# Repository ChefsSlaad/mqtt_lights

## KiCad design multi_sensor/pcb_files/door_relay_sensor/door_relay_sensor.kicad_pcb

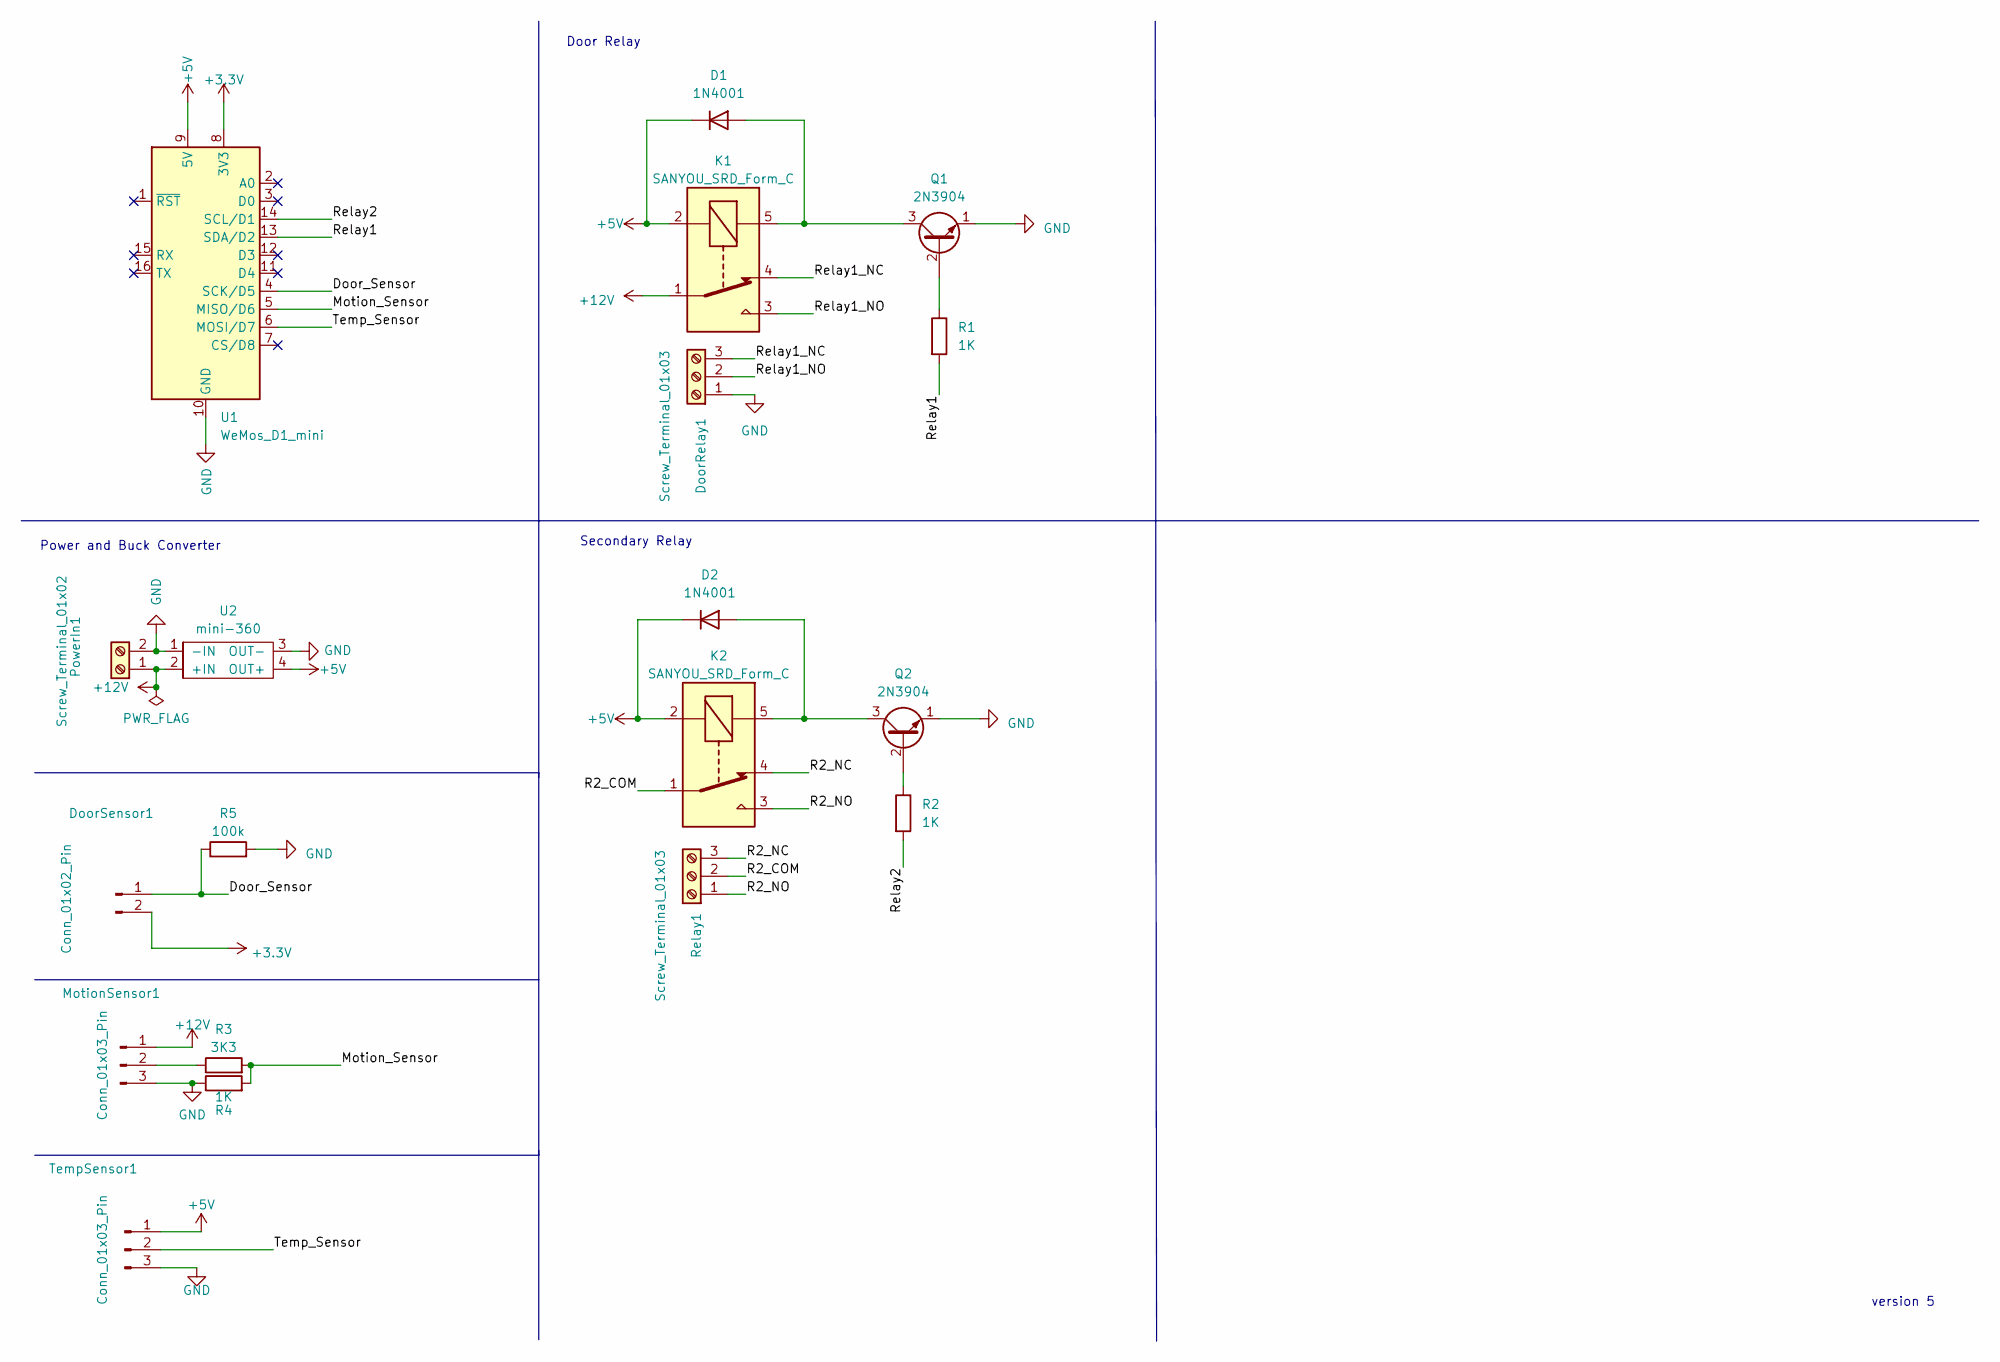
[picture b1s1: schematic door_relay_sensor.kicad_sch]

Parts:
D1, D2: 1N4001; D_DO-41_SOD81_P7.62mm_Horizontal
DoorRelay1: Screw_Terminal_01x03; TerminalBlock_bornier-3_P5.08mm
DoorSensor1: Conn_01x02_Pin; JST_EH_B2B-EH-A_1x02_P2.50mm_Vertical
K1, K2: SANYOU_SRD_Form_C; Relay_SPDT_SANYOU_SRD_Series_Form_C
MotionSensor1: Conn_01x03_Pin; JST_EH_B3B-EH-A_1x03_P2.50mm_Vertical
PowerIn1: Screw_Terminal_01x02; TerminalBlock_bornier-2_P5.08mm
Q1, Q2: 2N3904; TO-92_Wide
R1, R2, R4: 1K; R_Axial_DIN0207_L6.3mm_D2.5mm_P7.62mm_Horizontal
R3: 3K3; R_Axial_DIN0207_L6.3mm_D2.5mm_P7.62mm_Horizontal
R5: 100k; R_Axial_DIN0207_L6.3mm_D2.5mm_P7.62mm_Horizontal
Relay1: Screw_Terminal_01x03; TerminalBlock_bornier-3_P5.08mm
TempSensor1: Conn_01x03_Pin; JST_EH_B3B-EH-A_1x03_P2.50mm_Vertical
U1: WeMos_D1_mini; WEMOS_D1_mini_light
U2: mini-360; buck_converter 16.8x22,14

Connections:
+3.3V: DoorSensor1.2, U1.8 (3V3)
+5V: D1.1 (K), D2.1 (K), K1.2, K2.2, TempSensor1.1, U1.9 (5V), U2.4 (OUT+)
+12V: K1.1, MotionSensor1.1, PowerIn1.1, U2.2 (+IN)
/Door_Sensor: DoorSensor1.1, R5.1, U1.4 (SCK/D5)
/Motion_Sensor: R3.2, R4.2, U1.5 (MISO/D6)
/R2_COM: K2.1, Relay1.2
/R2_NC: K2.4, Relay1.3
/R2_NO: K2.3, Relay1.1
/Relay1: R1.2, U1.13 (SDA/D2)
/Relay1_NC: DoorRelay1.3, K1.4
/Relay1_NO: DoorRelay1.2, K1.3
/Relay2: R2.2, U1.14 (SCL/D1)
/Temp_Sensor: TempSensor1.2, U1.6 (MOSI/D7)
GND: DoorRelay1.1, MotionSensor1.3, PowerIn1.2, Q1.1 (E), Q2.1 (E), R4.1, R5.2, TempSensor1.3, U1.10 (GND), U2.1 (-IN), U2.3 (OUT-)
unnamed: D1.2 (A), K1.5, Q1.3 (C)
unnamed: D2.2 (A), K2.5, Q2.3 (C)
unnamed: MotionSensor1.2, R3.1
unnamed: Q1.2 (B), R1.1
unnamed: Q2.2 (B), R2.1

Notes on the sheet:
Power and Buck Converter
Secondary Relay
version 5
Door Relay

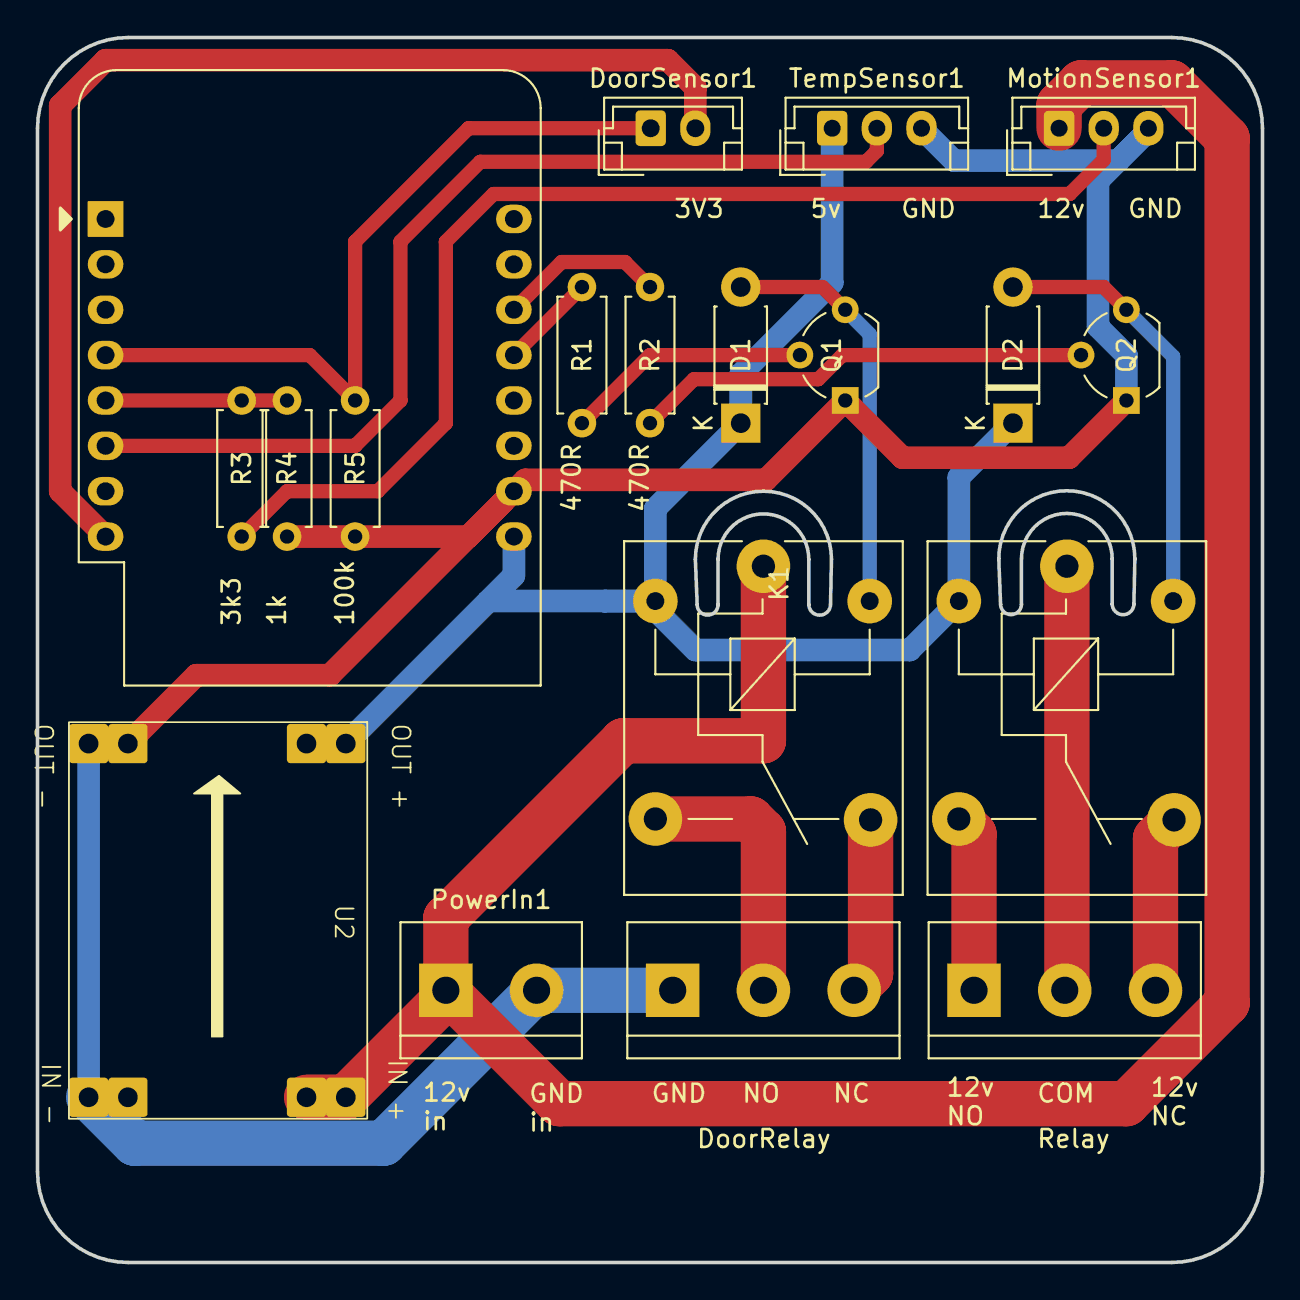
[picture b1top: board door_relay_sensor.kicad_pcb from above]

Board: 2 copper layers, 68.6 x 68.6 mm, 19 parts (0 on the bottom side), 19 nets.

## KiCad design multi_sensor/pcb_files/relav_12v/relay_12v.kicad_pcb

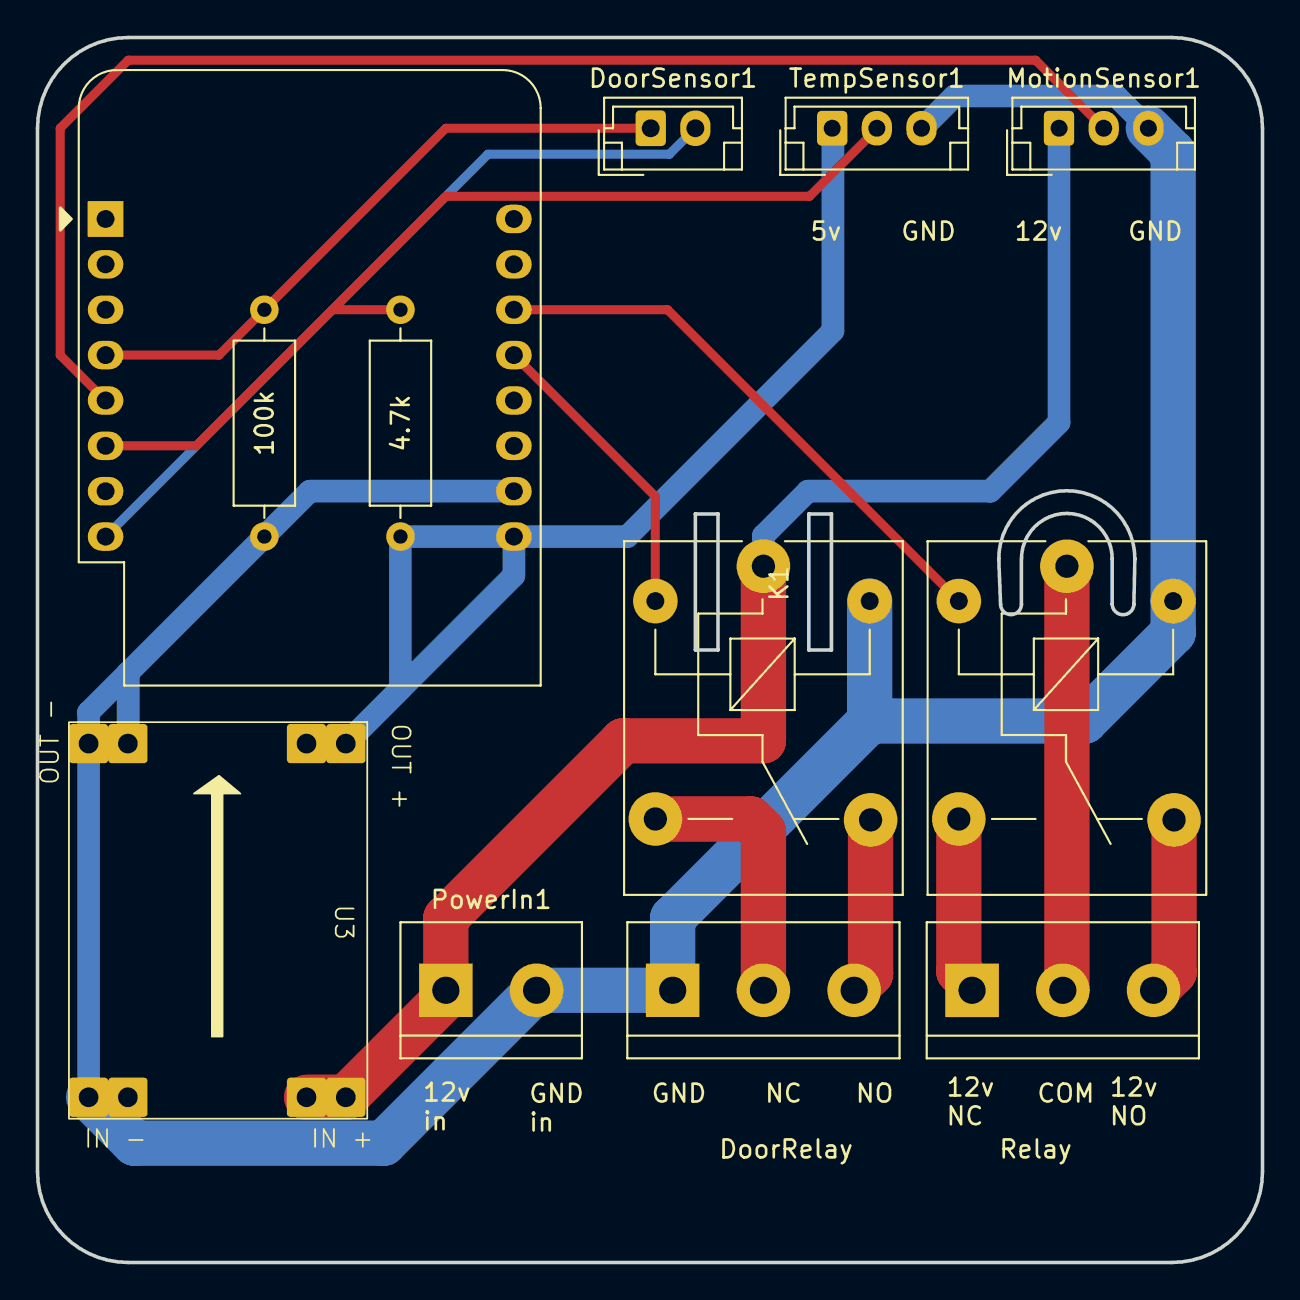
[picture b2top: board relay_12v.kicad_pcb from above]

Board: 2 copper layers, 68.6 x 68.6 mm, 12 parts (0 on the bottom side), 14 nets.

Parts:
DoorRelay: Screw_Terminal_01x03; TerminalBlock_bornier-3_P5.08mm
DoorSensor1: Conn_01x02_Pin; JST_EH_B2B-EH-A_1x02_P2.50mm_Vertical
K1, K2: SANYOU_SRD_Form_C; Relay_SPDT_SANYOU_SRD_Series_Form_C
MotionSensor1: Conn_01x03_Pin; JST_EH_B3B-EH-A_1x03_P2.50mm_Vertical
PowerIn1: Screw_Terminal_01x02; TerminalBlock_bornier-2_P5.08mm
R1: 100k; R_Axial_DIN0309_L9.0mm_D3.2mm_P12.70mm_Horizontal
R2: 4.7k; R_Axial_DIN0309_L9.0mm_D3.2mm_P12.70mm_Horizontal
Relay: Screw_Terminal_01x03; TerminalBlock_bornier-3_P5.08mm
TempSensor1: Conn_01x03_Pin; JST_EH_B3B-EH-A_1x03_P2.50mm_Vertical
U1: WeMos_D1_mini; WEMOS_D1_mini_light
U3: mini-360; buck_converter 16.8x22,14

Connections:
+3.3V: DoorSensor1.2, U1.8 (3V3)
+5V: R2.1, TempSensor1.1, U1.9 (5V), U3.4 (OUT+)
+12V: K1.1, MotionSensor1.1, PowerIn1.1, U3.2 (+IN)
/Door_Sensor: DoorSensor1.1, R1.1, U1.4 (SCK/D5)
/Motion_Sensor: MotionSensor1.2, U1.5 (MISO/D6)
/R2_COM: K2.1, Relay.2
/R2_NC: K2.4, Relay.3
/R2_NO: K2.3, Relay.1
/Relay1: K1.2, U1.13 (SDA/D2)
/Relay1_NC: DoorRelay.3, K1.4
/Relay1_NO: DoorRelay.2, K1.3
/Relay2: K2.2, U1.14 (SCL/D1)
/Temp_Sensor: R2.2, TempSensor1.2, U1.6 (MOSI/D7)
GND: DoorRelay.1, K1.5, K2.5, MotionSensor1.3, PowerIn1.2, R1.2, TempSensor1.3, U1.10 (GND), U3.1 (-IN), U3.3 (OUT-)

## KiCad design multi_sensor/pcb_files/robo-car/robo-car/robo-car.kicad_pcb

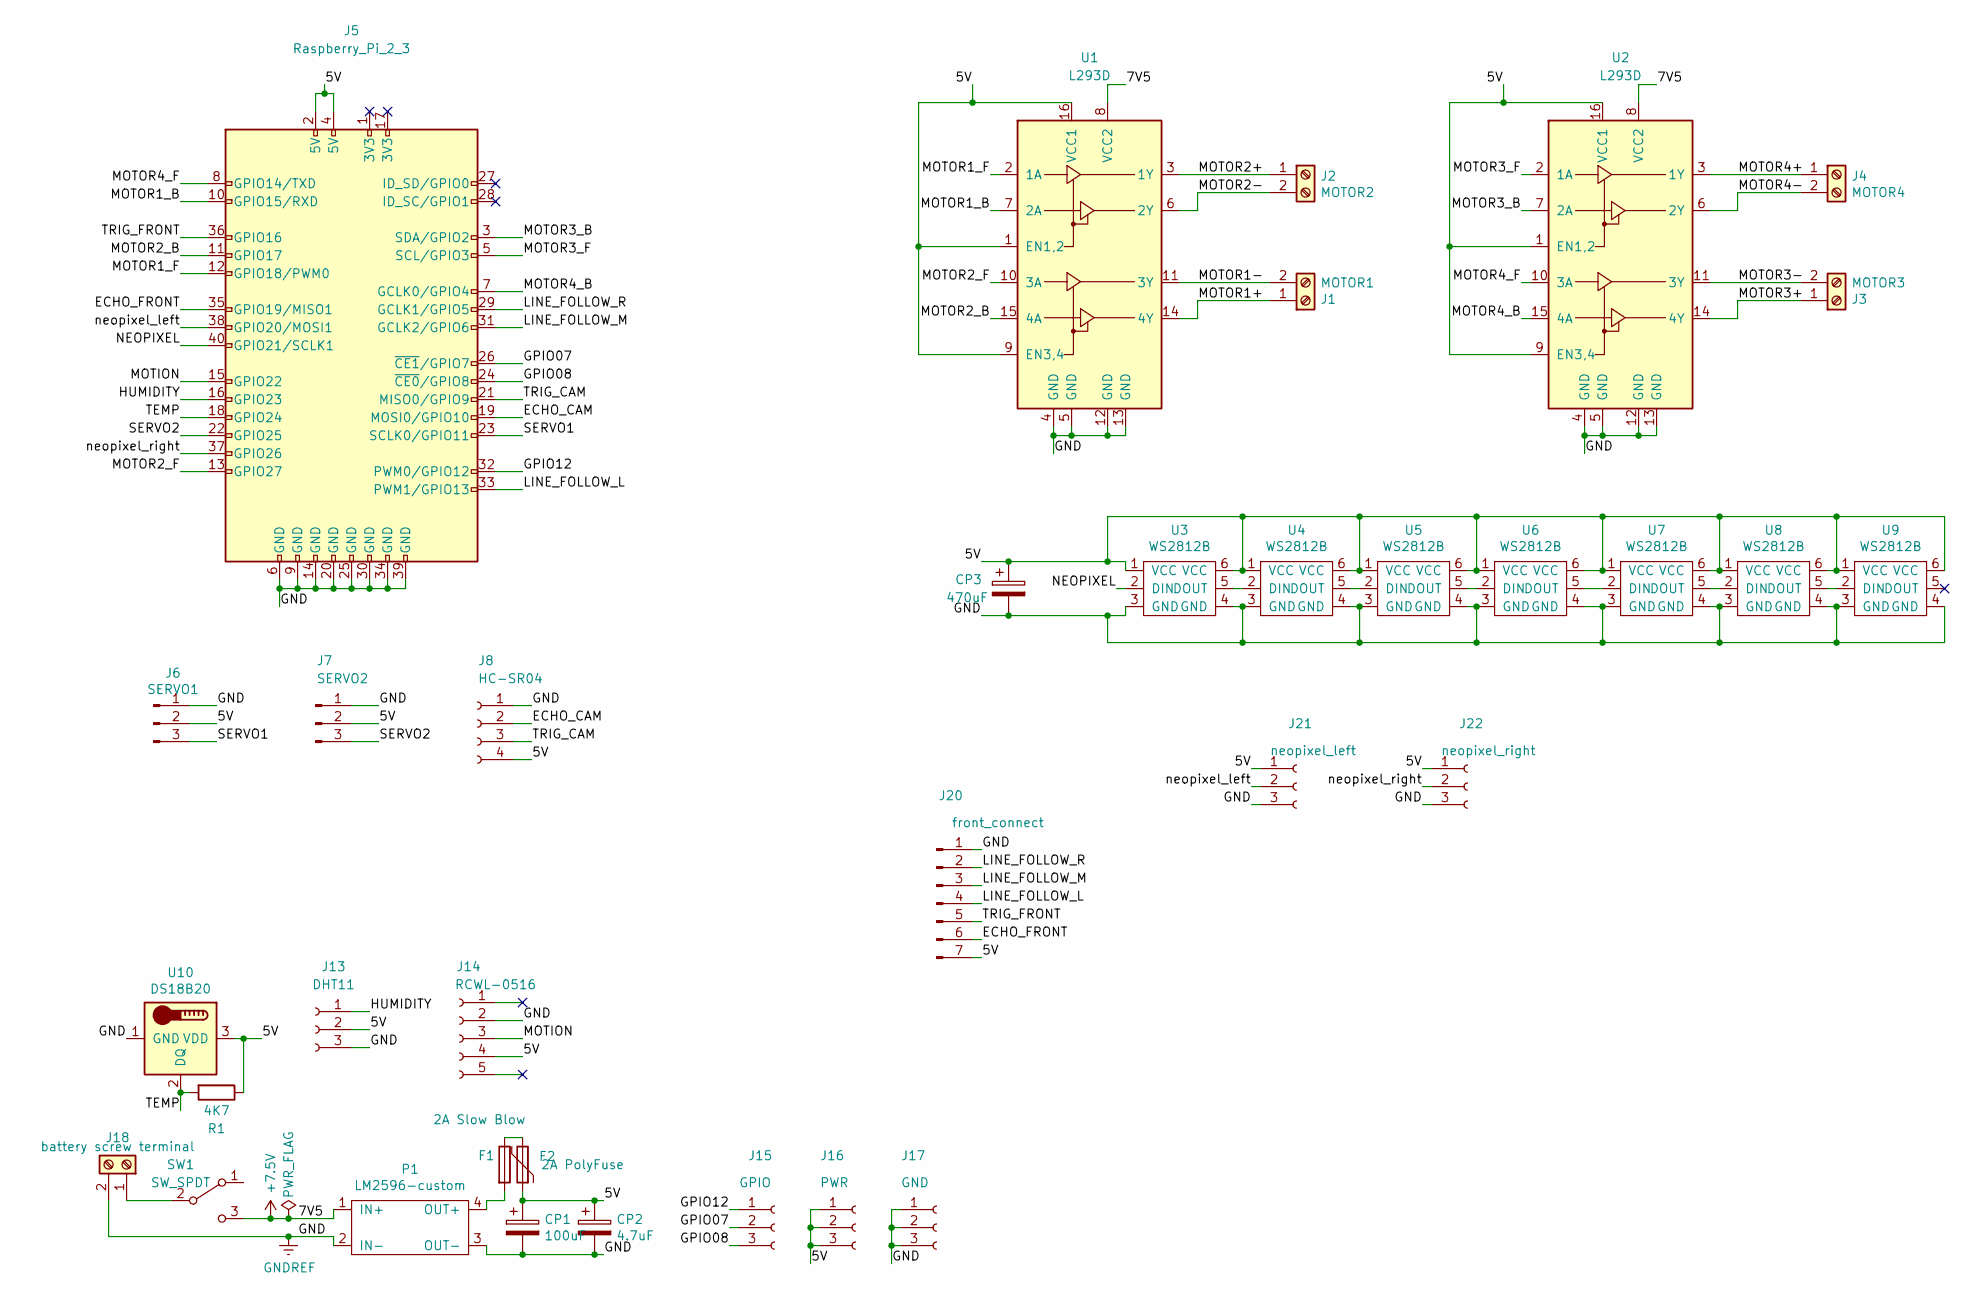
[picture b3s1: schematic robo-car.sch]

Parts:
CP1: 100uF; CP_Radial_D5.0mm_P2.50mm
CP2: 4.7uF; CP_Radial_D4.0mm_P2.00mm
CP3: 470uF; CP_Radial_D6.3mm_P2.50mm
F1: 2A Slow Blow; slow_blow_polyfuse
F2: 2A PolyFuse; restoring polyfuse
J1: MOTOR1; TerminalBlock_Altech_AK300-2_P5.00mm
J2: MOTOR2; TerminalBlock_Altech_AK300-2_P5.00mm
J3: MOTOR3; TerminalBlock_Altech_AK300-2_P5.00mm
J4: MOTOR4; TerminalBlock_Altech_AK300-2_P5.00mm
J5: Raspberry_Pi_2_3; PinSocket_2x20_P2.54mm_Vertical
J6: SERVO1; PinHeader_1x03_P2.54mm_Vertical
J7: SERVO2; PinHeader_1x03_P2.54mm_Vertical
J8: HC-SR04; PinSocket_1x04_P2.54mm_Vertical
J13: DHT11; PinSocket_1x03_P2.54mm_Vertical
J14: RCWL-0516; PinHeader_1x05_P2.54mm_Vertical
J15: GPIO; PinSocket_1x03_P2.54mm_Vertical
J16: PWR; PinSocket_1x03_P2.54mm_Vertical
J17: GND; PinSocket_1x03_P2.54mm_Vertical
J18: battery screw terminal; TerminalBlock_Altech_AK300-2_P5.00mm
J20: front_connect; PinHeader_1x07_P2.54mm_Vertical
J21: neopixel_left; JST_EH_B3B-EH-A_1x03_P2.50mm_Vertical
J22: neopixel_right; JST_EH_B3B-EH-A_1x03_P2.50mm_Vertical
P1: LM2596-custom; lm2596-custom
R1: 4K7; R_Axial_DIN0207_L6.3mm_D2.5mm_P7.62mm_Horizontal
SW1: SW_SPDT; rocker switch 8.5x3.5mm 2.54piych
U1, U2: L293D; DIP-16_W7.62mm
U3, U4, U5, U6, U7, U8, U9: WS2812B; neopixel_pcb
U10: DS18B20; TO-92_Inline

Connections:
+7.5V: P1.1 (IN+), SW1.3 (C), U1.8 (VCC2), U2.8 (VCC2)
/5V: CP1.1, CP2.1, CP3.1, F2.1, J5.2 (5V), J5.4 (5V), J6.2, J7.2, J8.4, J13.2, J14.4, J16.1, J16.2, J16.3, J20.7, J21.1, J22.1, R1.1, U1.1 (EN1,2), U1.9 (EN3,4), U1.16 (VCC1), U2.1 (EN1,2), U2.9 (EN3,4), U2.16 (VCC1), U3.1 (VCC), U3.6 (VCC), U4.1 (VCC), U4.6 (VCC), U5.1 (VCC), U5.6 (VCC), U6.1 (VCC), U6.6 (VCC), U7.1 (VCC), U7.6 (VCC), U8.1 (VCC), U8.6 (VCC), U9.1 (VCC), U9.6 (VCC), U10.3 (VDD)
/ECHO_CAM: J5.19 (MOSI0/GPIO10), J8.2
/ECHO_FRONT: J5.35 (GPIO19/MISO1), J20.6
/GPIO07: J5.26 (~CE1~/GPIO7), J15.2
/GPIO08: J5.24 (~CE0~/GPIO8), J15.3
/GPIO12: J5.32 (PWM0/GPIO12), J15.1
/HUMIDITY: J5.16 (GPIO23), J13.1
/LINE_FOLLOW_L: J5.33 (PWM1/GPIO13), J20.4
/LINE_FOLLOW_M: J5.31 (GCLK2/GPIO6), J20.3
/LINE_FOLLOW_R: J5.29 (GCLK1/GPIO5), J20.2
/MOTION: J5.15 (GPIO22), J14.3
/MOTOR1+: J1.1, U1.14 (4Y)
/MOTOR1-: J1.2, U1.11 (3Y)
/MOTOR1_B: J5.10 (GPIO15/RXD), U1.7 (2A)
/MOTOR1_F: J5.12 (GPIO18/PWM0), U1.2 (1A)
/MOTOR2+: J2.1, U1.3 (1Y)
/MOTOR2-: J2.2, U1.6 (2Y)
/MOTOR2_B: J5.11 (GPIO17), U1.15 (4A)
/MOTOR2_F: J5.13 (GPIO27), U1.10 (3A)
/MOTOR3+: J3.1, U2.14 (4Y)
/MOTOR3-: J3.2, U2.11 (3Y)
/MOTOR3_B: J5.3 (SDA/GPIO2), U2.7 (2A)
/MOTOR3_F: J5.5 (SCL/GPIO3), U2.2 (1A)
/MOTOR4+: J4.1, U2.3 (1Y)
/MOTOR4-: J4.2, U2.6 (2Y)
/MOTOR4_B: J5.7 (GCLK0/GPIO4), U2.15 (4A)
/MOTOR4_F: J5.8 (GPIO14/TXD), U2.10 (3A)
/NEOPIXEL: J5.40 (GPIO21/SCLK1), U3.2 (DIN)
/SERVO1: J5.23 (SCLK0/GPIO11), J6.3
/SERVO2: J5.22 (GPIO25), J7.3
/TEMP: J5.18 (GPIO24), R1.2, U10.2 (DQ)
/TRIG_CAM: J5.21 (MISO0/GPIO9), J8.3
/TRIG_FRONT: J5.36 (GPIO16), J20.5
/neopixel_left: J5.38 (GPIO20/MOSI1), J21.2
/neopixel_right: J5.37 (GPIO26), J22.2
GNDREF: CP1.2, CP2.2, CP3.2, J5.6 (GND), J5.9 (GND), J5.14 (GND), J5.20 (GND), J5.25 (GND), J5.30 (GND), J5.34 (GND), J5.39 (GND), J6.1, J7.1, J8.1, J13.3, J14.2, J17.1, J17.2, J17.3, J18.2, J20.1, J21.3, J22.3, P1.2 (IN-), P1.3 (OUT-), U1.4 (GND), U1.5 (GND), U1.12 (GND), U1.13 (GND), U2.4 (GND), U2.5 (GND), U2.12 (GND), U2.13 (GND), U3.3 (GND), U3.4 (GND), U4.3 (GND), U4.4 (GND), U5.3 (GND), U5.4 (GND), U6.3 (GND), U6.4 (GND), U7.3 (GND), U7.4 (GND), U8.3 (GND), U8.4 (GND), U9.3 (GND), U9.4 (GND), U10.1 (GND)
unnamed: F1.1, F2.2
unnamed: F1.2, P1.4 (OUT+)
unnamed: J18.1, SW1.2 (B)
unnamed: U3.5 (DOUT), U4.2 (DIN)
unnamed: U4.5 (DOUT), U5.2 (DIN)
unnamed: U5.5 (DOUT), U6.2 (DIN)
unnamed: U6.5 (DOUT), U7.2 (DIN)
unnamed: U7.5 (DOUT), U8.2 (DIN)
unnamed: U8.5 (DOUT), U9.2 (DIN)

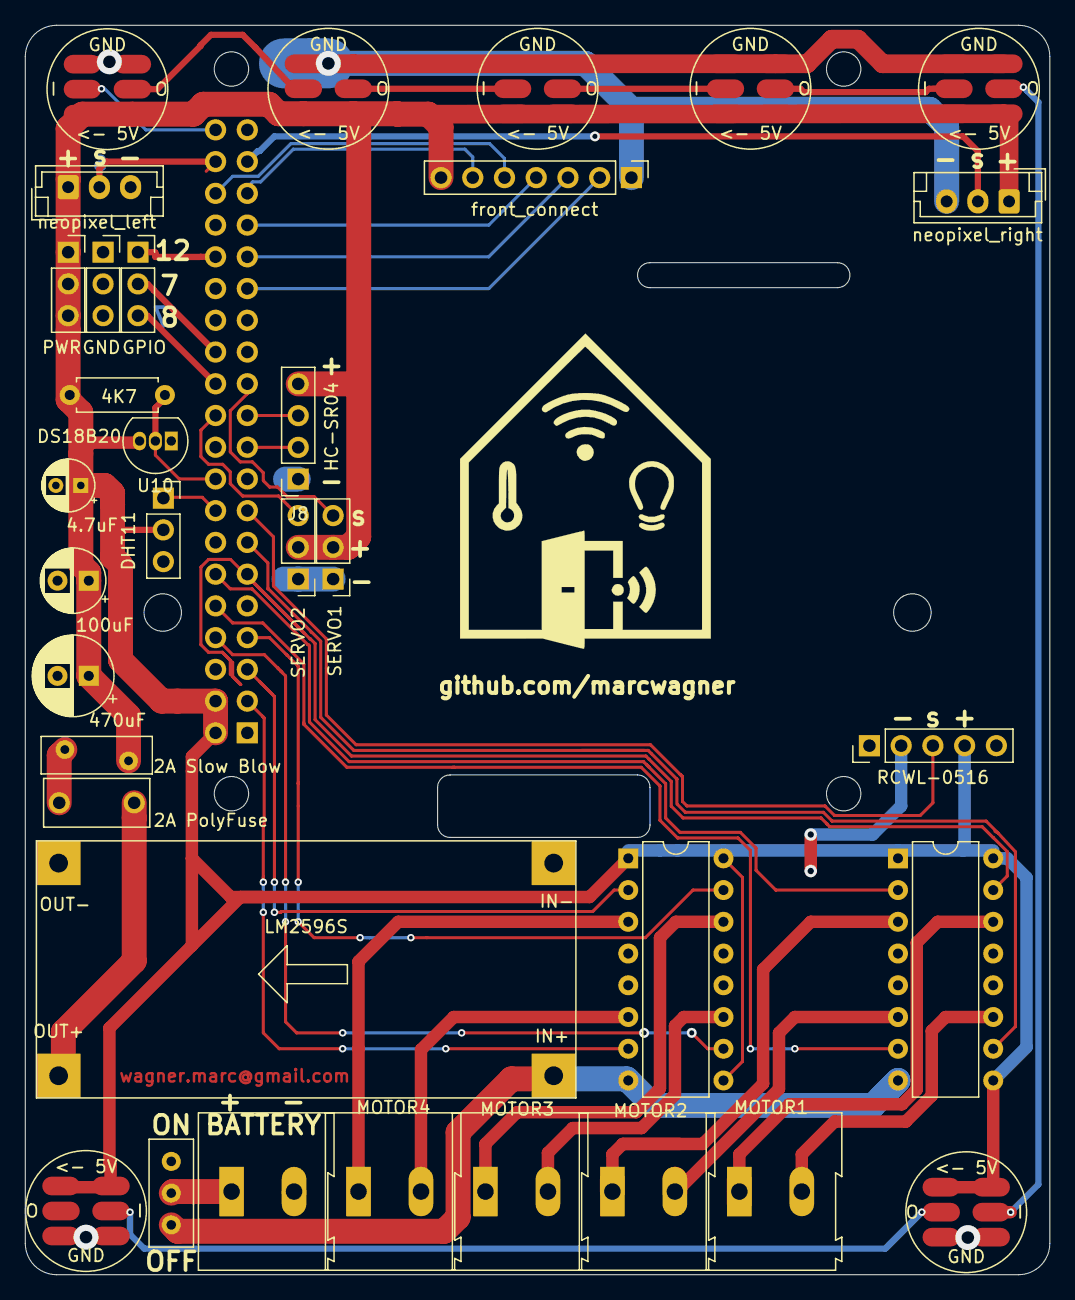
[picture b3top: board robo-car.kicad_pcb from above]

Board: 2 copper layers, 82.0 x 100.0 mm, 35 parts (1 on the bottom side), 46 nets.

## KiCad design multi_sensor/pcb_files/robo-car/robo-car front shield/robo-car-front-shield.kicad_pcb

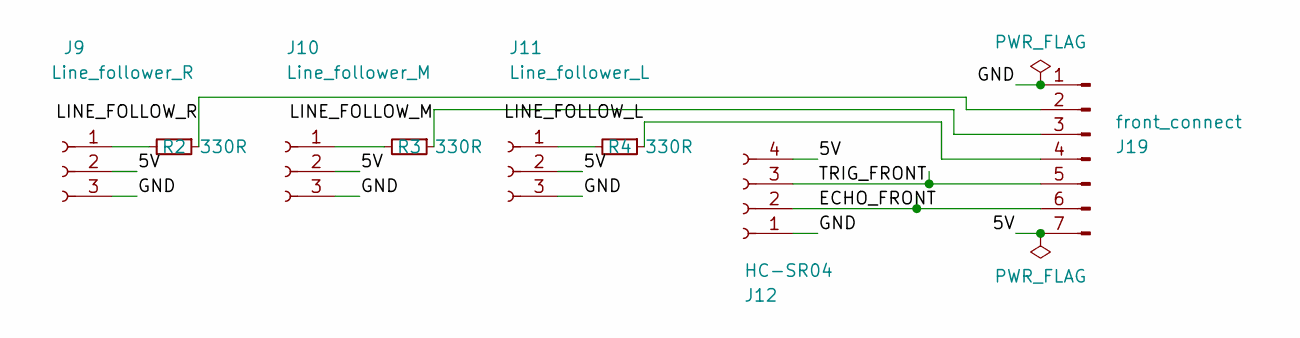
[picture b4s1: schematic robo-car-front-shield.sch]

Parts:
J9: Line_follower_R; linefollower
J10: Line_follower_M; linefollower
J11: Line_follower_L; linefollower
J12: HC-SR04; PinSocket_1x04_P2.54mm_Vertical
J19: front_connect; PinHeader_1x07_P2.54mm_Vertical
R2, R3, R4: 330R; R_Axial_DIN0207_L6.3mm_D2.5mm_P7.62mm_Horizontal

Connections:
/5V: J9.2, J10.2, J11.2, J12.4, J19.7
/ECHO_FRONT: J12.2, J19.6
/GND: J9.3, J10.3, J11.3, J12.1, J19.1
/LINE_FOLLOW_L: J19.4, R4.1
/LINE_FOLLOW_M: J19.3, R3.1
/LINE_FOLLOW_R: J19.2, R2.1
/TRIG_FRONT: J12.3, J19.5
unnamed: J9.1, R2.2
unnamed: J10.1, R3.2
unnamed: J11.1, R4.2

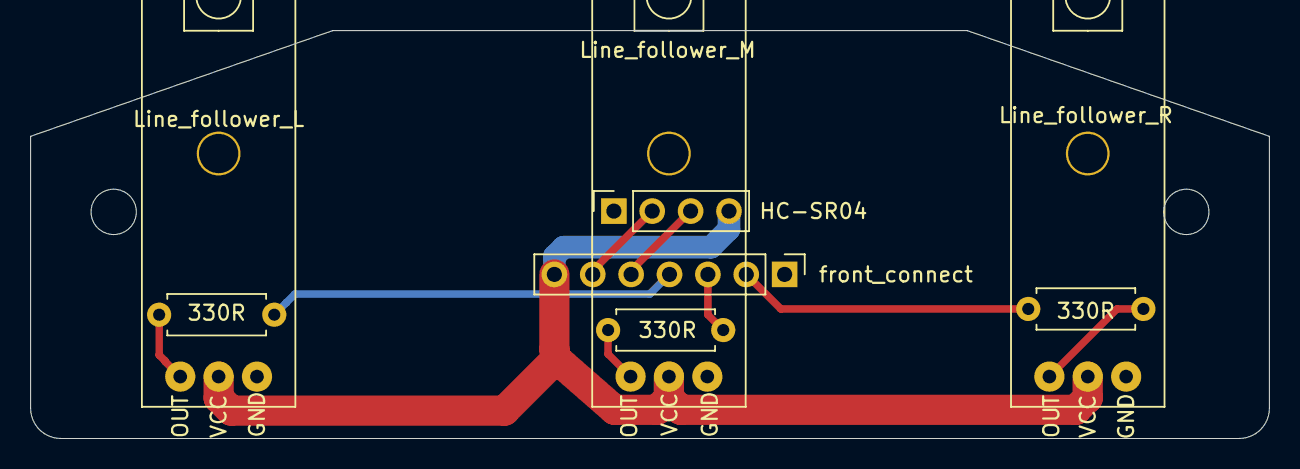
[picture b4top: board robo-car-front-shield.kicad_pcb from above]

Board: 2 copper layers, 82.0 x 27.0 mm, 8 parts (0 on the bottom side), 10 nets.

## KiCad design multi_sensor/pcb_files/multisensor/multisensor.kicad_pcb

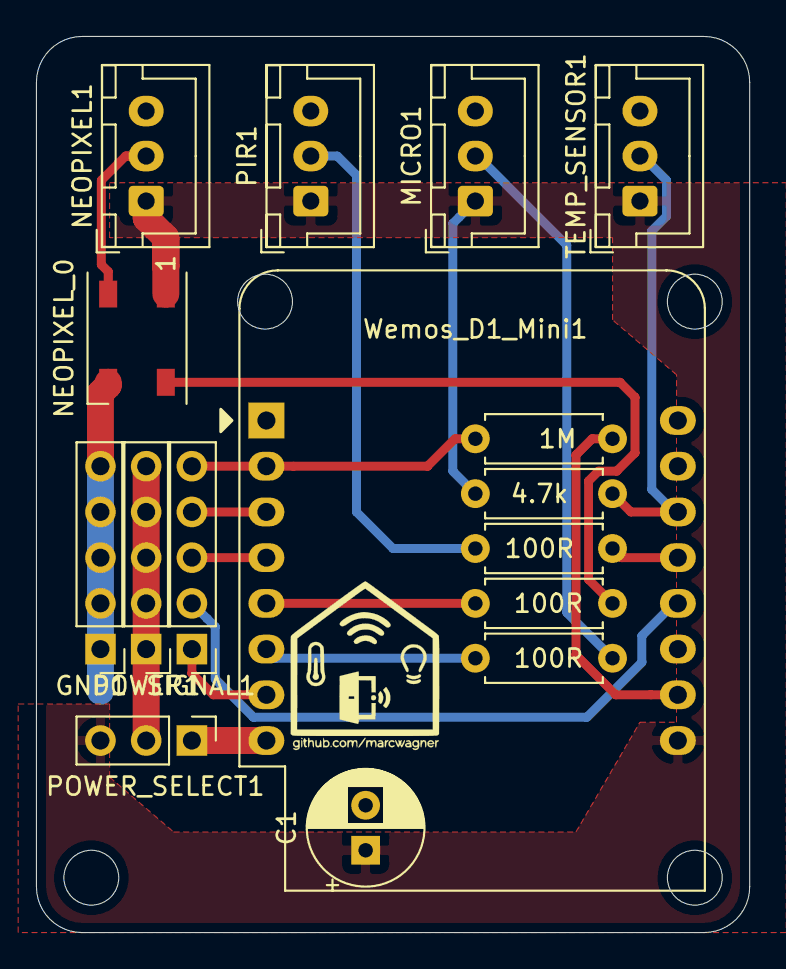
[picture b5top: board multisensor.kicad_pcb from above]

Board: 2 copper layers, 39.6 x 49.8 mm, 16 parts (0 on the bottom side), 17 nets.

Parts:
C1: 220uF 16V; CP_Radial_D6.3mm_P2.50mm
GND1: Conn_01x04_Male; PinHeader_1x05_P2.54mm_Vertical
MICRO1: Conn_01x03_Female; JST_XH_B3B-XH-A_1x03_P2.50mm_Vertical
NEOPIXEL1: Conn_01x03_Female; JST_XH_B3B-XH-A_1x03_P2.50mm_Vertical
NEOPIXEL_0: Inolux_IN-PI556FCH; LED_WS2812B_PLCC4_5.0x5.0mm_P3.2mm
PIR1: Conn_01x03_Female; JST_XH_B3B-XH-A_1x03_P2.50mm_Vertical
POWER1: Conn_01x04_Male; PinHeader_1x05_P2.54mm_Vertical
POWER_SELECT1: Conn_01x04_Male; PinHeader_1x03_P2.54mm_Vertical
R1, R2, R3: 100R; R_Axial_DIN0207_L6.3mm_D2.5mm_P7.62mm_Horizontal
R4: 4.7k; R_Axial_DIN0207_L6.3mm_D2.5mm_P7.62mm_Horizontal
R5: 1M; R_Axial_DIN0207_L6.3mm_D2.5mm_P7.62mm_Horizontal
SIGNAL1: Conn_01x05_Male; PinHeader_1x05_P2.54mm_Vertical
TEMP_SENSOR1: Conn_01x03_Female; JST_XH_B3B-XH-A_1x03_P2.50mm_Vertical
Wemos_D1_Mini1: WeMos_D1_mini; WEMOS_D1_mini_light

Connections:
+3V3: POWER_SELECT1.1, Wemos_D1_Mini1.8
+5V: C1.1, MICRO1.1, NEOPIXEL1.1, NEOPIXEL_0.1, PIR1.1, POWER_SELECT1.3, R4.1, TEMP_SENSOR1.1, Wemos_D1_Mini1.9
/ANALOG_S: R5.2, SIGNAL1.5, Wemos_D1_Mini1.2
/GPIO0_S: SIGNAL1.2, Wemos_D1_Mini1.12
/GPIO14_S: SIGNAL1.3, Wemos_D1_Mini1.4
/GPIO15_S: SIGNAL1.1, Wemos_D1_Mini1.7
/GPIO16_S: SIGNAL1.4, Wemos_D1_Mini1.3
/MICRO_S: R3.2, Wemos_D1_Mini1.6
/NEOPIXEL_S: R1.2, Wemos_D1_Mini1.5
/PIR_S: R2.2, Wemos_D1_Mini1.13
/POWER: POWER1.1, POWER1.2, POWER1.3, POWER1.4, POWER1.5, POWER_SELECT1.2
/TEMP_SENSOR_S: R4.2, TEMP_SENSOR1.2, Wemos_D1_Mini1.14
GND: C1.2, GND1.1, GND1.2, GND1.3, GND1.4, GND1.5, MICRO1.3, NEOPIXEL1.3, NEOPIXEL_0.3, PIR1.3, R5.1, TEMP_SENSOR1.3, Wemos_D1_Mini1.10
unnamed: MICRO1.2, R3.1
unnamed: NEOPIXEL1.2, NEOPIXEL_0.2
unnamed: NEOPIXEL_0.4, R1.1
unnamed: PIR1.2, R2.1

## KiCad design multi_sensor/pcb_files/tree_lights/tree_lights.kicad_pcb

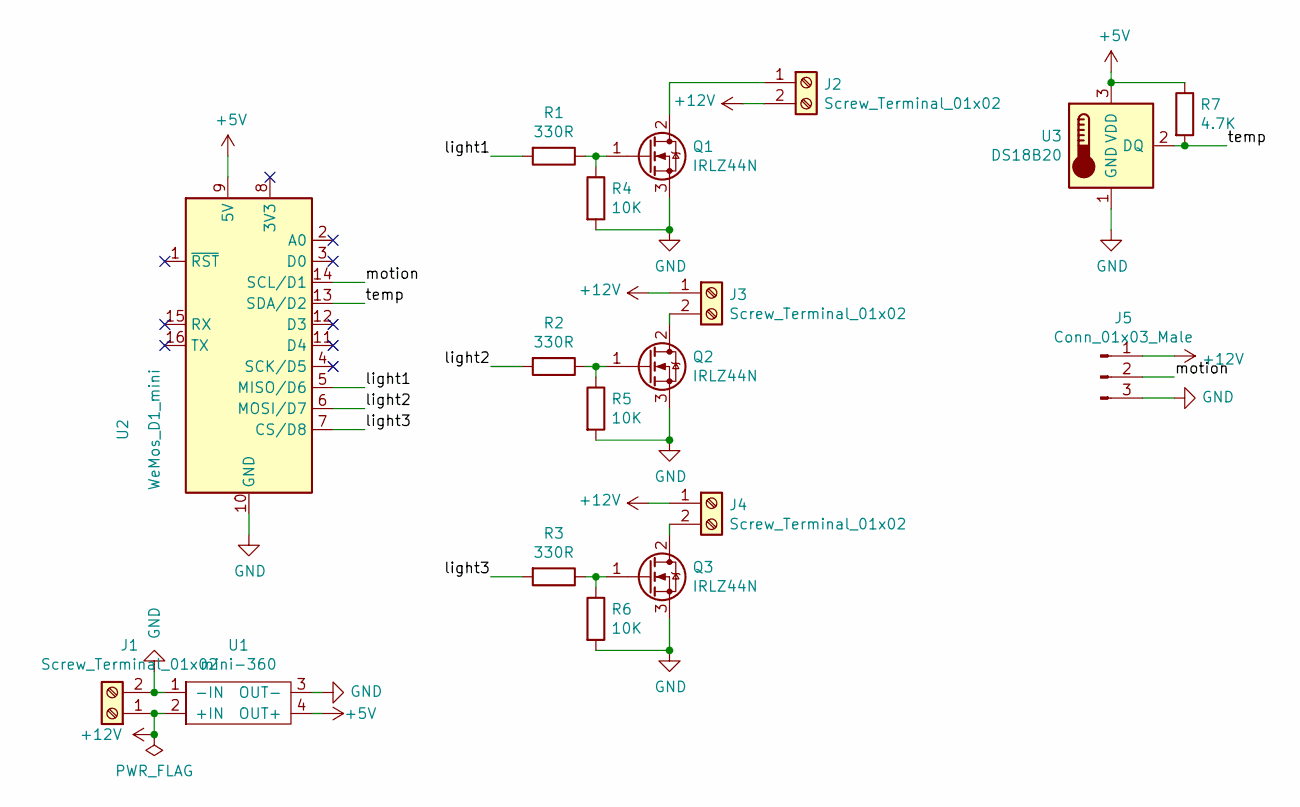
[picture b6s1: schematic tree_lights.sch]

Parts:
J1, J2, J3, J4: Screw_Terminal_01x02; TerminalBlock_Altech_AK300-2_P5.00mm
J5: Conn_01x03_Male; PinHeader_1x03_P2.54mm_Vertical
Q1, Q3: IRLZ44N; TO-220-3_Vertical
Q2: IRLZ44N; TO-220-3_Horizontal_TabDown
R1, R2, R3: 330R; R_Axial_DIN0207_L6.3mm_D2.5mm_P2.54mm_Vertical
R4, R5, R6: 10K; R_Axial_DIN0207_L6.3mm_D2.5mm_P2.54mm_Vertical
R7: 4.7K; R_Axial_DIN0207_L6.3mm_D2.5mm_P2.54mm_Vertical
U1: mini-360
U2: WeMos_D1_mini; wemos_d1_small
U3: DS18B20; TO-92_Inline

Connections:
+5V: R7.1, U1.4 (OUT+), U2.9 (5V), U3.3 (VDD)
+12V: J1.1, J2.2, J3.1, J4.1, J5.1, U1.2 (+IN)
/light1: R1.2, U2.5 (MISO/D6)
/light2: R2.2, U2.6 (MOSI/D7)
/light3: R3.2, U2.7 (CS/D8)
/motion: J5.2, U2.14 (SCL/D1)
/temp: R7.2, U2.13 (SDA/D2), U3.2 (DQ)
GND: J1.2, J5.3, Q1.3 (S), Q2.3 (S), Q3.3 (S), R4.2, R5.2, R6.2, U1.1 (-IN), U1.3 (OUT-), U2.10 (GND), U3.1 (GND)
unnamed: J2.1, Q1.2 (D)
unnamed: J3.2, Q2.2 (D)
unnamed: J4.2, Q3.2 (D)
unnamed: Q1.1 (G), R1.1, R4.1
unnamed: Q2.1 (G), R2.1, R5.1
unnamed: Q3.1 (G), R3.1, R6.1

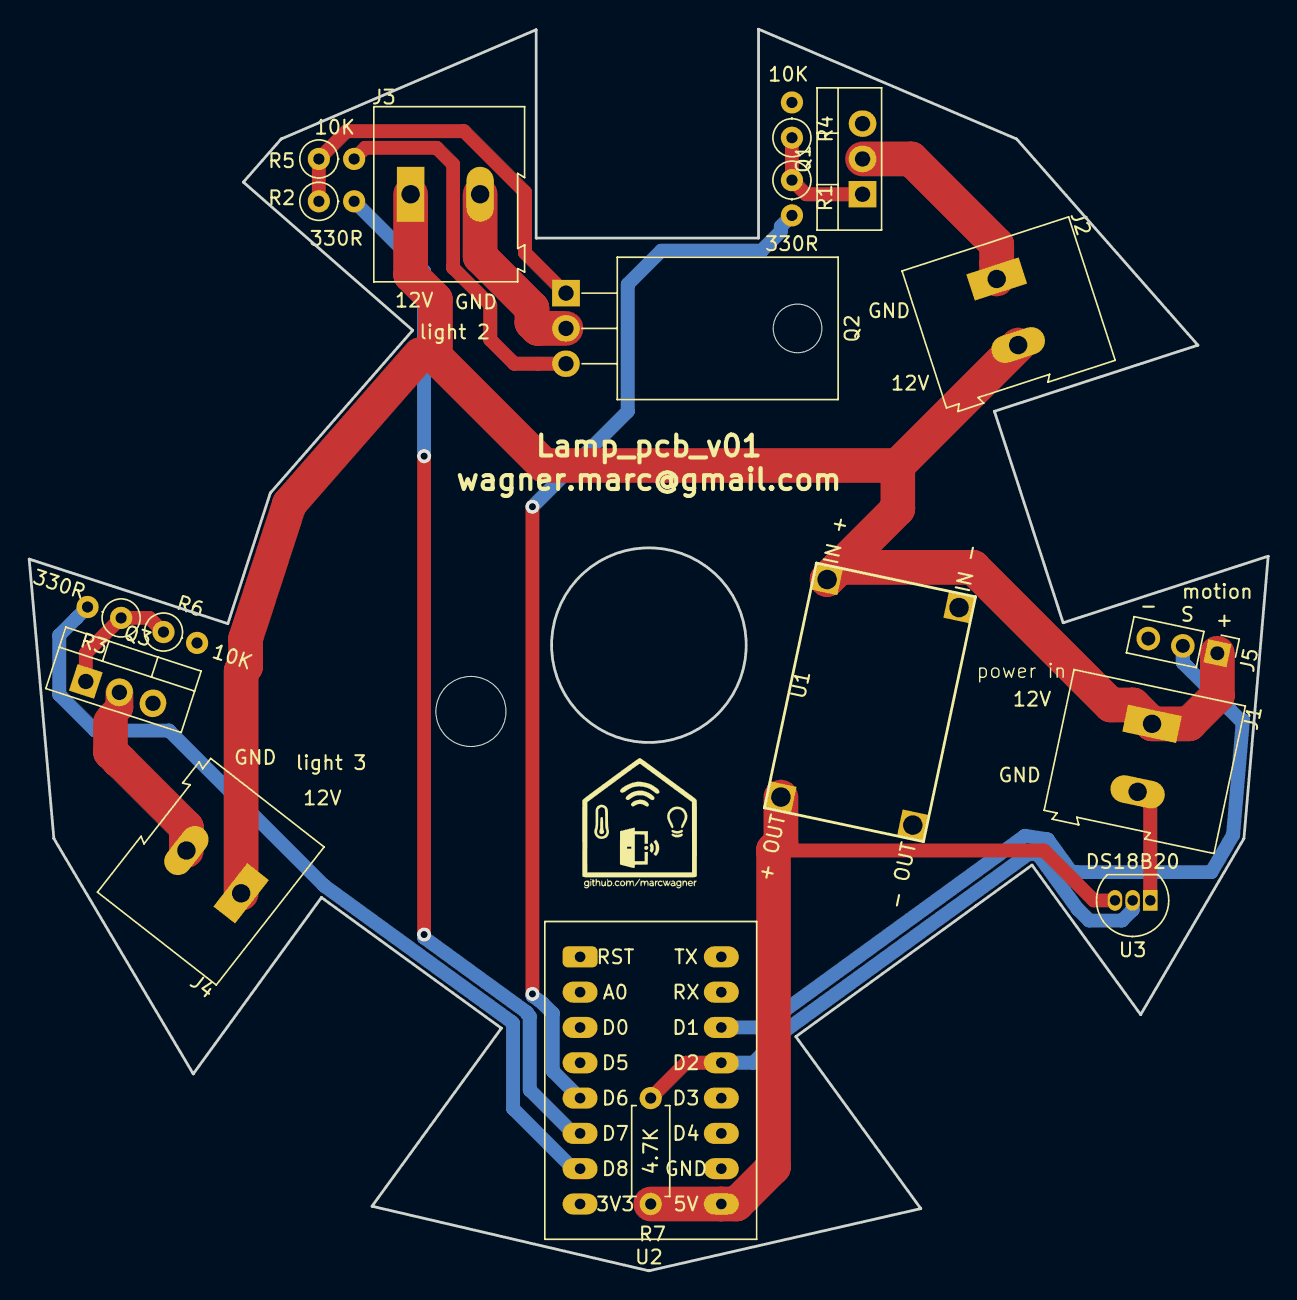
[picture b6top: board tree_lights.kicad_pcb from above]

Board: 2 copper layers, 89.1 x 89.3 mm, 18 parts (0 on the bottom side), 14 nets.
